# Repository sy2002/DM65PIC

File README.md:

# Firmware for the DM65PIC
## MEGA65 Computer

MEGA65 is an open-source new and open C65-like computer.
All hardware designs and all software are open-source (LGPL).
Please visit www.mega65.org to learn more about it.

## Quickstart

Click here: [How to flash the firmware on the DM65PIC](bin/README.md)

## DM65PIC Peripheral Interface Controller
The DM65PIC is the peripheral interface controller for the MEGA65 computer.
It is based on the [STM32F4 microcontroller](http://www.st.com/stm32f4).

The purpose of the DM65PIC is to provide an interface to an original
Commodore 65 prototype keyboard or a standard C64 keyboard and to provide
joystick ports. Future versions will also be able to work with the MEGA65
custom keyboard and these keyboards will also be able to be used as standard
USB HID devices e.g. while using emulators. Additionally we will implement the
Commodore 65 user port in future versions.

Here is a foto of some prototype version of our custom PCB:

This GitHub repository is containing the firmware of the DM65PIC.

You can see a combination of a MEGA65 FPGA prototype (based on a Nexys 4 DDR
board), a DMPIC65 prototype and a very first work-in-progress version of the
firmware in conjuncton with a real Commodore 65 prototype keyboard in action
on YouTube: [https://youtu.be/5PpsEw80j3M](https://youtu.be/5PpsEw80j3M).

### Folder structure
```
00-STM32F4xx_STANDARD_PERIPHERAL_DRIVERS  STM32 CMSIS and standard peripheral drivers
00-STM32F429_LIBRARIES                    Tilen Majerle's STM32F4 library
01-DM65PIC                                Firmware for the DM65PIC
bin                                       Firmware binary and how-to-flash documentation
eagle                                     Hardware design for the PCB
```

The actual firmware is located within the file `main.c` in the folder
`01-DM65PIC/01-DM65PIC/User`.

### How to flash
In the folder `bin` you always find the latest binary version of the firmware
as a `.hex` file. There is also the file `bin/README.md` that explains you
how to build a cable and how to flash the DM65PIC firmware using a Windows,
OSX or Linux machine.

### How to build
We used the free version of [Keil uVision5](http://www.keil.com/uvision/).
The free version is code-size constrained (32KB), but as our compiled firmware
(including all the libs) is smaller than 32KB, the free version works fine.

After having installed the Keil IDE, just double click or open the file
`project.uvprojx` in the `01-DM65PIC` folder. As all paths are relative, you
should be able to build without further modifications.

### How the interface works
The DM65PIC is doing a matrix scan on the original Commodore 65 keyboard by
letting current flow through the columns and then find out if a key is pressed
by checking, if the current from the column arrives at a certain row. That
means, we configure all "column pins" of the STM32 microcontroller as outputs
(no pullup/pulldown resistor) and all "row pins" as inputs (pulldown
resistor).

The following diagram is the basis for the matrix scan. It is taken from
Commodore's original document
[c65manual.txt](http://www.zimmers.net/cbmpics/cbm/c65/c65manual.txt)
([permalink](https://perma.cc/E5R3-MEXA)),
chapter 2.1.2.

```

            +-----+-----+-----+-----+-----+-----+-----+-----+-----+            +-----+
            | C0  | C1  | C2  | C3  | C4  | C5  | C6  | C7  | C8  |            | GND |
            |PIN20|PIN19|PIN18|PIN17|PIN16|PIN15|PIN14|PIN13|PIN-4|            |PIN-1|
            +--+--+--+--+--+--+--+--+--+--+--+--+--+--+--+--+--+--+            +--+--+
               |     |     |     |     |     |     |     |     |                  |
               |     |     |     |     |     |     |     |     |                  |
               V     V     V     V     V     V     V     V     V                  |
+-----+     +-----+-----+-----+-----+-----+-----+-----+-----+-----+               |
| R0  |<----+ INS |  #  |  %  |  '  |  )  |  +  | œ   |  !  | NO  |               |
|PIN12|     | DEL |  3  |  5  |  7  |  9  |     |     |  1  | SCRL|               |
+-----+     +-----+-----+-----+-----+-----+-----+-----+-----+-----+               |
| R1  |<----+ RET |  W  |  R  |  Y  |  I  |  P  |  *  | <-- | TAB |               |
|PIN11|     |     |     |     |     |     |     |     |     |     |               |
+-----+     +-----+-----+-----+-----+-----+-----+-----+-----+-----+               |
| R2  |<----+ HORZ|  A  |  D  |  G  |  J  |  L  |  ]  | CTRL| ALT |               |
|PIN10|     | CRSR|     |     |     |     |     |  ;  |     |     +----------+    |
+-----+     +-----+-----+-----+-----+-----+-----+-----+-----+-----+          |    |
| R3  |<----+ F8  |  $  |  &  |  {  |  0  |  -  | CLR |  "  | HELP|          |    |
|PIN-9|     | F7  |  4  |  6  |  8  |     |     | HOM |  2  |     |          |    |
+-----+     +-----+-----+-----+-----+-----+-----+-----+-----+-----+          |    |
| R4  |<----+ F2  |  Z  |  C  |  B  |  M  |  >  |RIGHT|SPACE| F10 |          |    |
|PIN-8|     | F1  |     |     |     |     |  .  |SHIFT| BAR | F9  |          |    |
+-----+     +-----+-----+-----+-----+-----+-----+-----+-----+-----+          |    |
| R5  |<----+ F4  |  S  |  F  |  H  |  K  |  [  |  =  | C=  | F12 |          |    |
|PIN-7|     | F3  |     |     |     |     |  :  |     |     | F11 |          |    |
+-----+     +-----+-----+-----+-----+-----+-----+-----+-----+-----+          |    |
| R6  |<----+ F6  |  E  |  T  |  U  |  O  |  @  |  ã  |  Q  | F14 |          |    |
|PIN-6|     | F5  |     |     |     |     |     |  ^  |     | F13 |          |    |
+-----+     +-----+-----+-----+-----+-----+-----+-----+-----+-----+          |    |
| R7  |<----+ VERT|LEFT |  X  |  V  |  N  |  <  |  ?  | RUN | ESC +------+   |    |
|PIN-5|     | CRSR|SHIFT|     |     |     |  ,  |  /  | STOP|     +--+   |   |    |
+-----+     +--+--+--+--+-----+-----+-----+-----+--+--+-----+-----+  |   |   |    |
               |     |                             |                 |   |   |    |
               |     |                             |                 |   |   |    |
               |  +--+--+     /      (LOCKING)     |                 |   |   |    |
               |  |SHIFT+----+  +------------------------------------+   |   |    |
               |  | LOCK|                          |                     |   |    |
               |  +-----+                          |                     |   |    |
               |                             +-----+-----+               |   |    |
            +--+--+                          |           |               |   |    |
            |CRSR +------------+-------------+           +---------------+   |    |
            | UP  |        K1 PIN-21         |           |                   |    |
            +--+--+                          |   4066    |                   |    |
               |                             |  DECODER  |                   |    |
            +--+--+                          |           |                   |    |
            |CRSR +------------+-------------+           +-------------------+    |
            |LEFT |        K2 PIN-22         |           |                        |
            +-----+                          +-----------+                        |
                                                                                  |
+-----+           +-----+     /                                                   |
| NMI | <---------+RESTR+----+  +-------------------------------------------------+
|PIN-3|           |     |                                                         |
+-----+           +-----+                                                         |
                                                                                  |
                                                                                  |
+-----+           +-----+     /      (LOCKING)                                    |
| R8  | <---------+CAPS +----+  +-------------------------------------------------+
|PIN-2|           |LOCK |
+-----+           +-----+

Keyboard Notes:

1. The  64 keys under C0 through C7 occupy the same matrix position as
   in the C/64,  as does the RESTORE key.  Including SHIFT-LOCK, there
   are 66 such keys.

2. The  extended  keyboard consists of the 8 keys under the C8 output.
   Counting the CAPS-LOCK key, there are 9 new keys. The C/64 does not
   scan these keys.

3. The new CURSOR LEFT and CURSOR UP keys simulate a CURSOR plus RIGHT
   SHIFT key combination.

4. The  keyboard mechanism will be mechanically similar to that of the
   C128.
```

While scanning the matrix, the DM65PIC firmware stores the status of each
single key in an array, that is then transmitted to the MEGA65 FPGA using
the Nexys 4 DDR's General Purpose IO (GPIO) port "JB".

The protocol between the DM65PIC and the FPGA works like this: Cyclically,
128-bit are transmitted as 32 (4-bit) nibbles. Each nibble represents 4 bit
within the above-mentioned matrix. Nibble #0 represents the keys INS/DEL,
RET, HORZ/CRSR, F8/F7. Nibble #1 represents F2/F1, F4/F3, F6/F5, VERT/CRSR.
And so on. Here is the full description of the data sequence:

```
nbls #0 - #17:   keyboard bits corresponding to the 9 columns of keys (see above)
nbl #18:         joystick 1: bit0=up, bit1=down, bit2=left, bit3=right
nbl #19:         bit0=joy1 fire, bit2=capslock key status, bit3=restore key status
nbl #20:         joystick 2: bit0=up, bit1=down, bit2=left, bit3=right
nbl #21:         bit0=joy2 fire, bit3=reset momentary-action switch status
nbl #22 onwards: expansion port connector
```

The nibbles are transmitted by setting below-mentioned "bit0" .. "bit3" pins
of the "JB" port and then clocking pin "JB1". For synchronizing the
transmission, the "start of sequence" pin "JB2" is used as soon as a new
128-bit package starts.

The FPGA is also able to communicate back to the DM65PIC, i.e. for transmitting
the LED status; but this is not supported, yet in the current version of the
firmware.

Here is the pin layout for the FPGA's "JB" port:

```
JB1  = PG8:  clock; data must be valid before rising edge
JB2  = PG9:  start of sequence, set to 1 on first nibble of a new 128bit sequence
JB3  = PG10: bit0 of output data nibble
JB4  = PG11: bit1 of output data nibble
JB7  = PG12: bit2 of output data nibble
JB8  = PG13: bit3 of output data nibble
JB9  = PG14: bit 0 of input bit pair
JB10 = PG15: bit 1 of input bit pair
```

### Credits
* [Paul Gardner-Stephen](http://c65gs.blogspot.de): MEGA65 main developer
* [Deft](http://www.m-e-g-a.org/de/mega/profile): chief MEGA65 officer
* doubleflash: DM65PIC hardware design
* [sy2002](http://www.sy2002.de): DM65PIC firmware in this GitHub repository

Special thanks go to [Tilen Majerle](https://github.com/MaJerle) for
supporting sy2002 in learning how to work with the STM32 toolchain and of
course for creating the awesome [STM32F4 library](https://stm32f4-discovery.net)
that we heavily used for creating the DM65PIC firmware.

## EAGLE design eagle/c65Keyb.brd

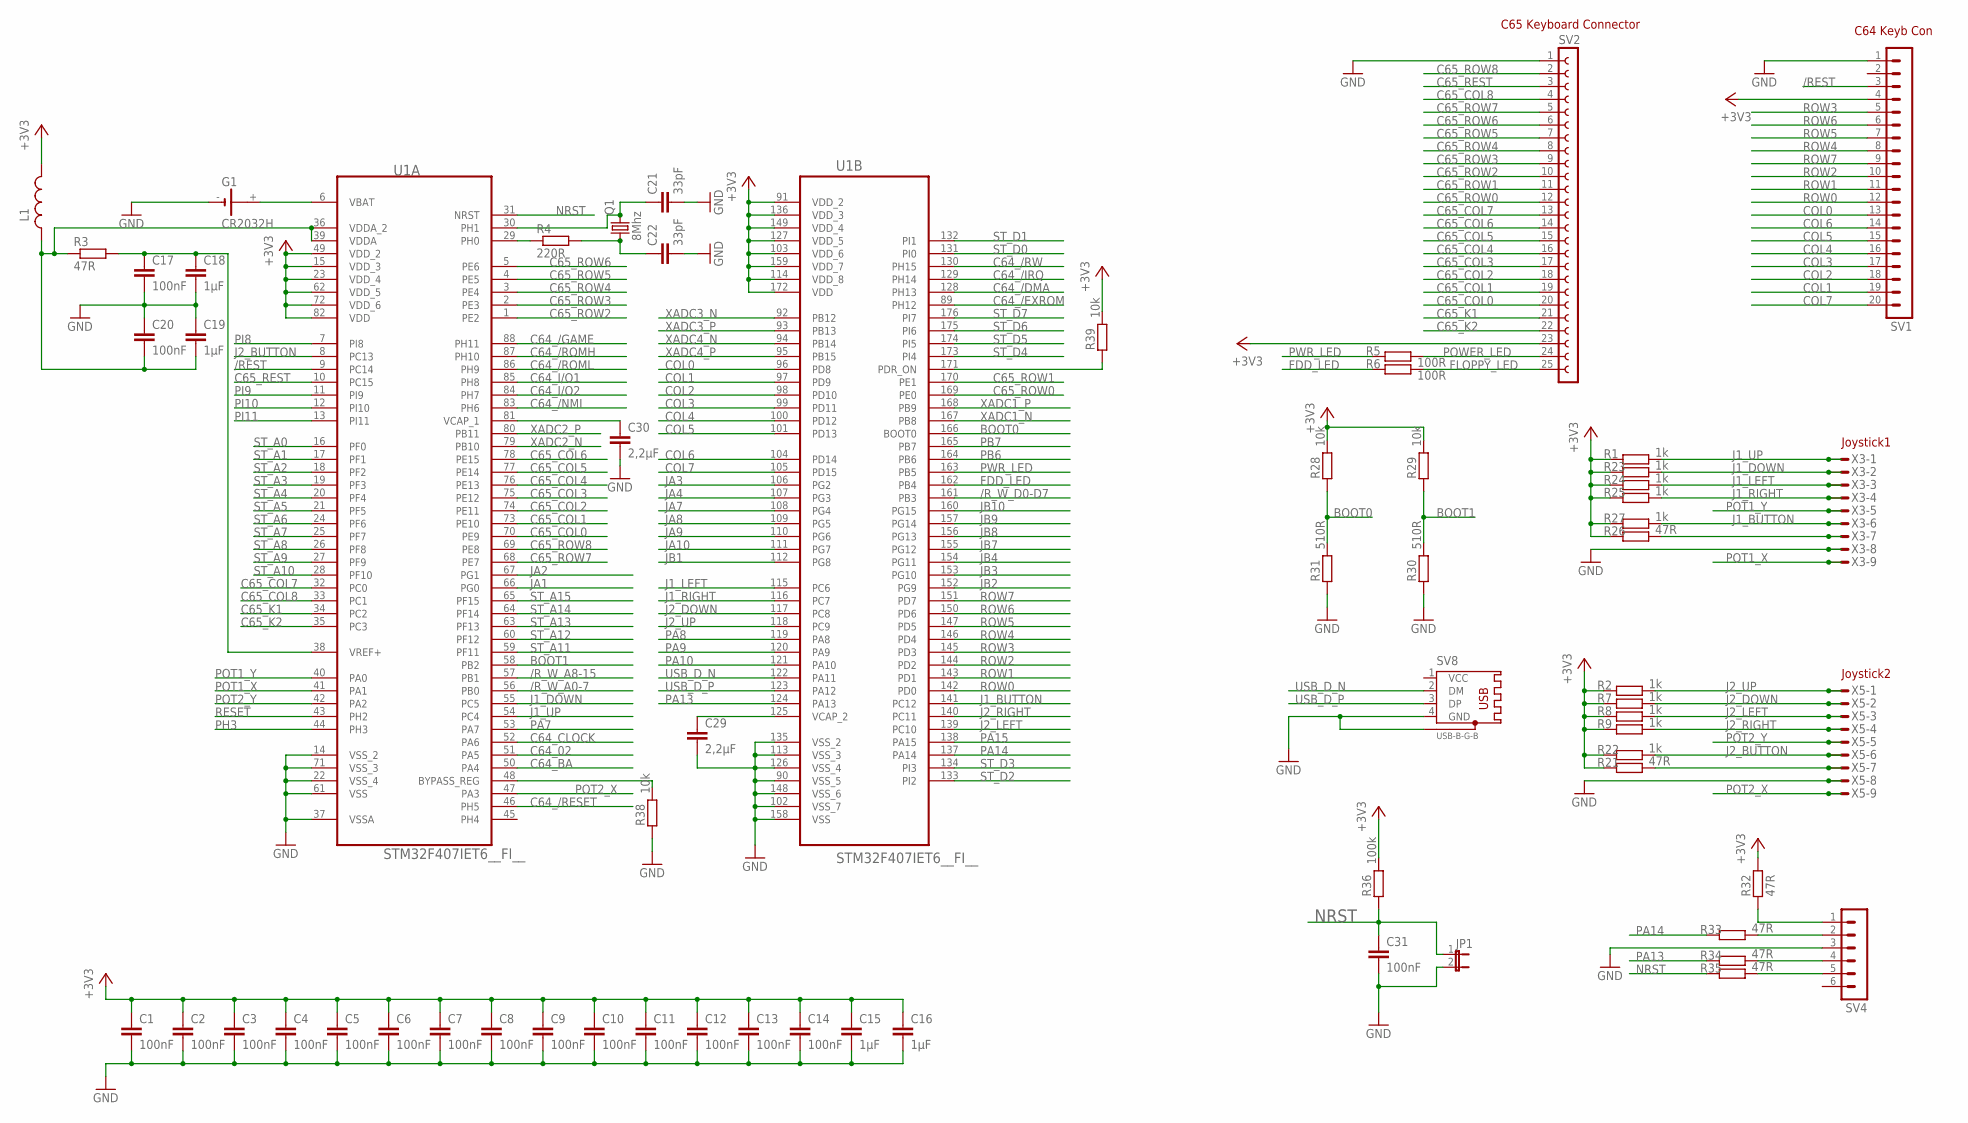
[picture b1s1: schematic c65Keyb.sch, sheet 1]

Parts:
C1, C2, C3, C4, C5, C6, C7, C8, C9, C10, C11, C12, C13, C14, C17, C20, C31: 100nF; C0805
C15, C16, C18, C19: 1µF; C0805
C21, C22: 33pF; C0805
C29, C30: 2,2µF; C0805
G1: CR2032H
JP1: JP1E; JP1
L1: L-0805A; SMD0805-ALT
Q1: 8Mhz; HC49UP
R1, R2, R7, R8, R9, R22, R23, R24, R25, R27: 1k; R0805
R3, R21, R26, R32, R33, R34, R35: 47R; R0805
R4: 220R; R0805
R5, R6: 100R; R0805
R28, R29, R38, R39: 10k; R0805
R30, R31: 510R; R0805
R36: 100k; R0805
SV1: MA20-1
SV2: C65_MOLEX_KEYB
SV4: MA06-1
SV8: USB-B-G-B; USB-B-THG-01
U1: STM32F407IET6__FI__; QFP176
X3, X5: M09-182S; 182-009-MALE

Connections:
+3V3: C1.1, C2.1, C3.1, C4.1, C5.1, C6.1, C7.1, C8.1, C9.1, C10.1, C11.1, C12.1, C13.1, C14.1, C15.1, C16.1, L1.2, R1.1, R2.1, R7.1, R8.1, R9.1, R21.1, R22.1, R23.1, R24.1, R25.1, R26.1, R27.1, R28.2, R29.2, R32.2, R36.2, R39.2, SV1.4, SV2.23, U1.15 (VDD_3), U1.23 (VDD_4), U1.49 (VDD_2), U1.62 (VDD_5), U1.72 (VDD_6), U1.82 (VDD), U1.91 (VDD_2), U1.103 (VDD_6), U1.114 (VDD_8), U1.127 (VDD_5), U1.136 (VDD_3), U1.149 (VDD_4), U1.159 (VDD_7), U1.172 (VDD); also elsewhere on the board
/REST: SV1.3, U1.9 (PC14)
/R_W_A0-7: U1.56 (PB0); also elsewhere on the board
/R_W_A8-15: U1.57 (PB1); also elsewhere on the board
/R_W_D0-D7: U1.161 (PB3); also elsewhere on the board
BOOT0: R28.1, R31.2, U1.166 (BOOT0)
BOOT1: R29.1, R30.2, U1.58 (PB2)
C64_02: U1.51 (PA5); also elsewhere on the board
C64_/DMA: U1.128 (PH13); also elsewhere on the board
C64_/EXROM: U1.89 (PH12); also elsewhere on the board
C64_/GAME: U1.88 (PH11); also elsewhere on the board
C64_/IRQ: U1.129 (PH14); also elsewhere on the board
C64_/NMI: U1.83 (PH6); also elsewhere on the board
C64_/RESET: U1.46 (PH5); also elsewhere on the board
C64_/ROMH: U1.87 (PH10); also elsewhere on the board
C64_/ROML: U1.86 (PH9); also elsewhere on the board
C64_/RW: U1.130 (PH15); also elsewhere on the board
C64_BA: U1.50 (PA4); also elsewhere on the board
C64_CLOCK: U1.52 (PA6); also elsewhere on the board
C64_I/O1: U1.85 (PH8); also elsewhere on the board
C64_I/O2: U1.84 (PH7); also elsewhere on the board
C65_COL0: SV2.20, U1.70 (PE9)
C65_COL1: SV2.19, U1.73 (PE10)
C65_COL2: SV2.18, U1.74 (PE11)
C65_COL3: SV2.17, U1.75 (PE12)
C65_COL4: SV2.16, U1.76 (PE13)
C65_COL5: SV2.15, U1.77 (PE14)
C65_COL6: SV2.14, U1.78 (PE15)
C65_COL7: SV2.13, U1.32 (PC0)
C65_COL8: SV2.4, U1.33 (PC1)
C65_K1: SV2.21, U1.34 (PC2)
C65_K2: SV2.22, U1.35 (PC3)
C65_REST: SV2.3, U1.10 (PC15)
C65_ROW0: SV2.12, U1.169 (PE0)
C65_ROW1: SV2.11, U1.170 (PE1)
C65_ROW2: SV2.10, U1.1 (PE2)
C65_ROW3: SV2.9, U1.2 (PE3)
C65_ROW4: SV2.8, U1.3 (PE4)
C65_ROW5: SV2.7, U1.4 (PE5)
C65_ROW6: SV2.6, U1.5 (PE6)
C65_ROW7: SV2.5, U1.68 (PE7)
C65_ROW8: SV2.2, U1.69 (PE8)
COL0: SV1.13, U1.96 (PD8)
COL1: SV1.19, U1.97 (PD9)
COL2: SV1.18, U1.98 (PD10)
COL3: SV1.17, U1.99 (PD11)
COL4: SV1.16, U1.100 (PD12)
COL5: SV1.15, U1.101 (PD13)
COL6: SV1.14, U1.104 (PD14)
COL7: SV1.20, U1.105 (PD15)
FDD_LED: R6.1, U1.162 (PB4)
FLOPPY_LED: R6.2, SV2.25
GND: C1.2, C2.2, C3.2, C4.2, C5.2, C6.2, C7.2, C8.2, C9.2, C10.2, C11.2, C12.2, C13.2, C14.2, C15.2, C16.2, C17.2, C18.2, C19.1, C20.1, C21.2, C22.2, C29.2, C30.2, C31.2, G1.-, JP1.2, R30.1, R31.1, R38.1, SV1.1, SV2.1, SV4.3, SV8.4 (GND), SV8.G1, U1.14 (VSS_2), U1.22 (VSS_4), U1.37 (VSSA), U1.61 (VSS), U1.71 (VSS_3), U1.90 (VSS_5), U1.102 (VSS_7), U1.113 (VSS_3), U1.126 (VSS_4), U1.135 (VSS_2), U1.148 (VSS_6), U1.158 (VSS), X3.8, X5.8; also elsewhere on the board
J1_BUTTON: R27.2, U1.141 (PC12), X3.6
J1_DOWN: R23.2, U1.55 (PC5), X3.2
J1_LEFT: R24.2, U1.115 (PC6), X3.3
J1_RIGHT: R25.2, U1.116 (PC7), X3.4
J1_UP: R1.2, U1.54 (PC4), X3.1
J2_BUTTON: R22.2, U1.8 (PC13), X5.6
J2_DOWN: R7.2, U1.117 (PC8), X5.2
J2_LEFT: R8.2, U1.139 (PC10), X5.3
J2_RIGHT: R9.2, U1.140 (PC11), X5.4
J2_UP: R2.2, U1.118 (PC9), X5.1
JA1: U1.66 (PG0); also elsewhere on the board
JA2: U1.67 (PG1); also elsewhere on the board
JA3: U1.106 (PG2); also elsewhere on the board
JA4: U1.107 (PG3); also elsewhere on the board
JA7: U1.108 (PG4); also elsewhere on the board
JA8: U1.109 (PG5); also elsewhere on the board
JA9: U1.110 (PG6); also elsewhere on the board
JA10: U1.111 (PG7); also elsewhere on the board
JB1: U1.112 (PG8); also elsewhere on the board
JB2: U1.152 (PG9); also elsewhere on the board
JB3: U1.153 (PG10); also elsewhere on the board
JB4: U1.154 (PG11); also elsewhere on the board
JB7: U1.155 (PG12); also elsewhere on the board
JB8: U1.156 (PG13); also elsewhere on the board
JB9: U1.157 (PG14); also elsewhere on the board
JB10: U1.160 (PG15); also elsewhere on the board
unnamed: G1.+, U1.6 (VBAT)
unnamed: R4.1, U1.29 (PH0)
unnamed: C17.1, C18.1, R3.2, U1.38 (VREF+)
unnamed: R21.2, X5.7
unnamed: C30.1, U1.81 (VCAP_1)
unnamed: C29.1, U1.125 (VCAP_2)
unnamed: R32.1, SV4.1
unnamed: R33.2, SV4.2
unnamed: R34.2, SV4.4
unnamed: R26.2, X3.7
unnamed: R35.2, SV4.5
unnamed: R38.2, U1.48 (BYPASS_REG)
unnamed: C21.1, Q1.2, U1.30 (PH1)
unnamed: C22.1, Q1.1, R4.2
unnamed: R39.1, U1.171 (PDR_ON)
unnamed: C19.2, C20.2, L1.1, R3.1, U1.36 (VDDA_2), U1.39 (VDDA)
NRST: C31.1, JP1.1, R35.1, R36.1, U1.31 (NRST)
PA7: U1.53 (PA7); also elsewhere on the board
PA8: U1.119 (PA8); also elsewhere on the board
PA9: U1.120 (PA9); also elsewhere on the board
PA10: U1.121 (PA10); also elsewhere on the board
PA13: R34.1, U1.124 (PA13)
PA14: R33.1, U1.137 (PA14)
PA15: U1.138 (PA15); also elsewhere on the board
PB6: U1.164 (PB6); also elsewhere on the board
PB7: U1.165 (PB7); also elsewhere on the board
PH3: U1.44 (PH3); also elsewhere on the board
PI8: U1.7 (PI8); also elsewhere on the board
PI9: U1.11 (PI9); also elsewhere on the board
PI10: U1.12 (PI10); also elsewhere on the board
PI11: U1.13 (PI11); also elsewhere on the board
POT1_X: U1.41 (PA1), X3.9
POT1_Y: U1.40 (PA0), X3.5
POT2_X: U1.47 (PA3), X5.9
POT2_Y: U1.42 (PA2), X5.5
POWER_LED: R5.2, SV2.24
PWR_LED: R5.1, U1.163 (PB5)
RESET: U1.43 (PH2); also elsewhere on the board
ROW0: SV1.12, U1.142 (PD0)
ROW1: SV1.11, U1.143 (PD1)
ROW2: SV1.10, U1.144 (PD2)
ROW3: SV1.5, U1.145 (PD3)
ROW4: SV1.8, U1.146 (PD4)
ROW5: SV1.7, U1.147 (PD5)
ROW6: SV1.6, U1.150 (PD6)
ROW7: SV1.9, U1.151 (PD7)
ST_A0: U1.16 (PF0); also elsewhere on the board
ST_A1: U1.17 (PF1); also elsewhere on the board
ST_A2: U1.18 (PF2); also elsewhere on the board
ST_A3: U1.19 (PF3); also elsewhere on the board
ST_A4: U1.20 (PF4); also elsewhere on the board
ST_A5: U1.21 (PF5); also elsewhere on the board
ST_A6: U1.24 (PF6); also elsewhere on the board
ST_A7: U1.25 (PF7); also elsewhere on the board
ST_A8: U1.26 (PF8); also elsewhere on the board
ST_A9: U1.27 (PF9); also elsewhere on the board
ST_A10: U1.28 (PF10); also elsewhere on the board
ST_A11: U1.59 (PF11); also elsewhere on the board
ST_A12: U1.60 (PF12); also elsewhere on the board
ST_A13: U1.63 (PF13); also elsewhere on the board
ST_A14: U1.64 (PF14); also elsewhere on the board
ST_A15: U1.65 (PF15); also elsewhere on the board
ST_D0: U1.131 (PI0); also elsewhere on the board
ST_D1: U1.132 (PI1); also elsewhere on the board
ST_D2: U1.133 (PI2); also elsewhere on the board
ST_D3: U1.134 (PI3); also elsewhere on the board
ST_D4: U1.173 (PI4); also elsewhere on the board
ST_D5: U1.174 (PI5); also elsewhere on the board
ST_D6: U1.175 (PI6); also elsewhere on the board
ST_D7: U1.176 (PI7); also elsewhere on the board
USB_D_N: SV8.2 (DM), U1.122 (PA11)
USB_D_P: SV8.3 (DP), U1.123 (PA12)
XADC1_N: U1.167 (PB8); also elsewhere on the board
XADC1_P: U1.168 (PB9); also elsewhere on the board
XADC2_N: U1.79 (PB10); also elsewhere on the board
XADC2_P: U1.80 (PB11); also elsewhere on the board
XADC3_N: U1.92 (PB12); also elsewhere on the board
XADC3_P: U1.93 (PB13); also elsewhere on the board
XADC4_N: U1.94 (PB14); also elsewhere on the board
XADC4_P: U1.95 (PB15); also elsewhere on the board

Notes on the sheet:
C64 Keyb Con
Joystick1
Joystick2
C65 Keyboard Connector

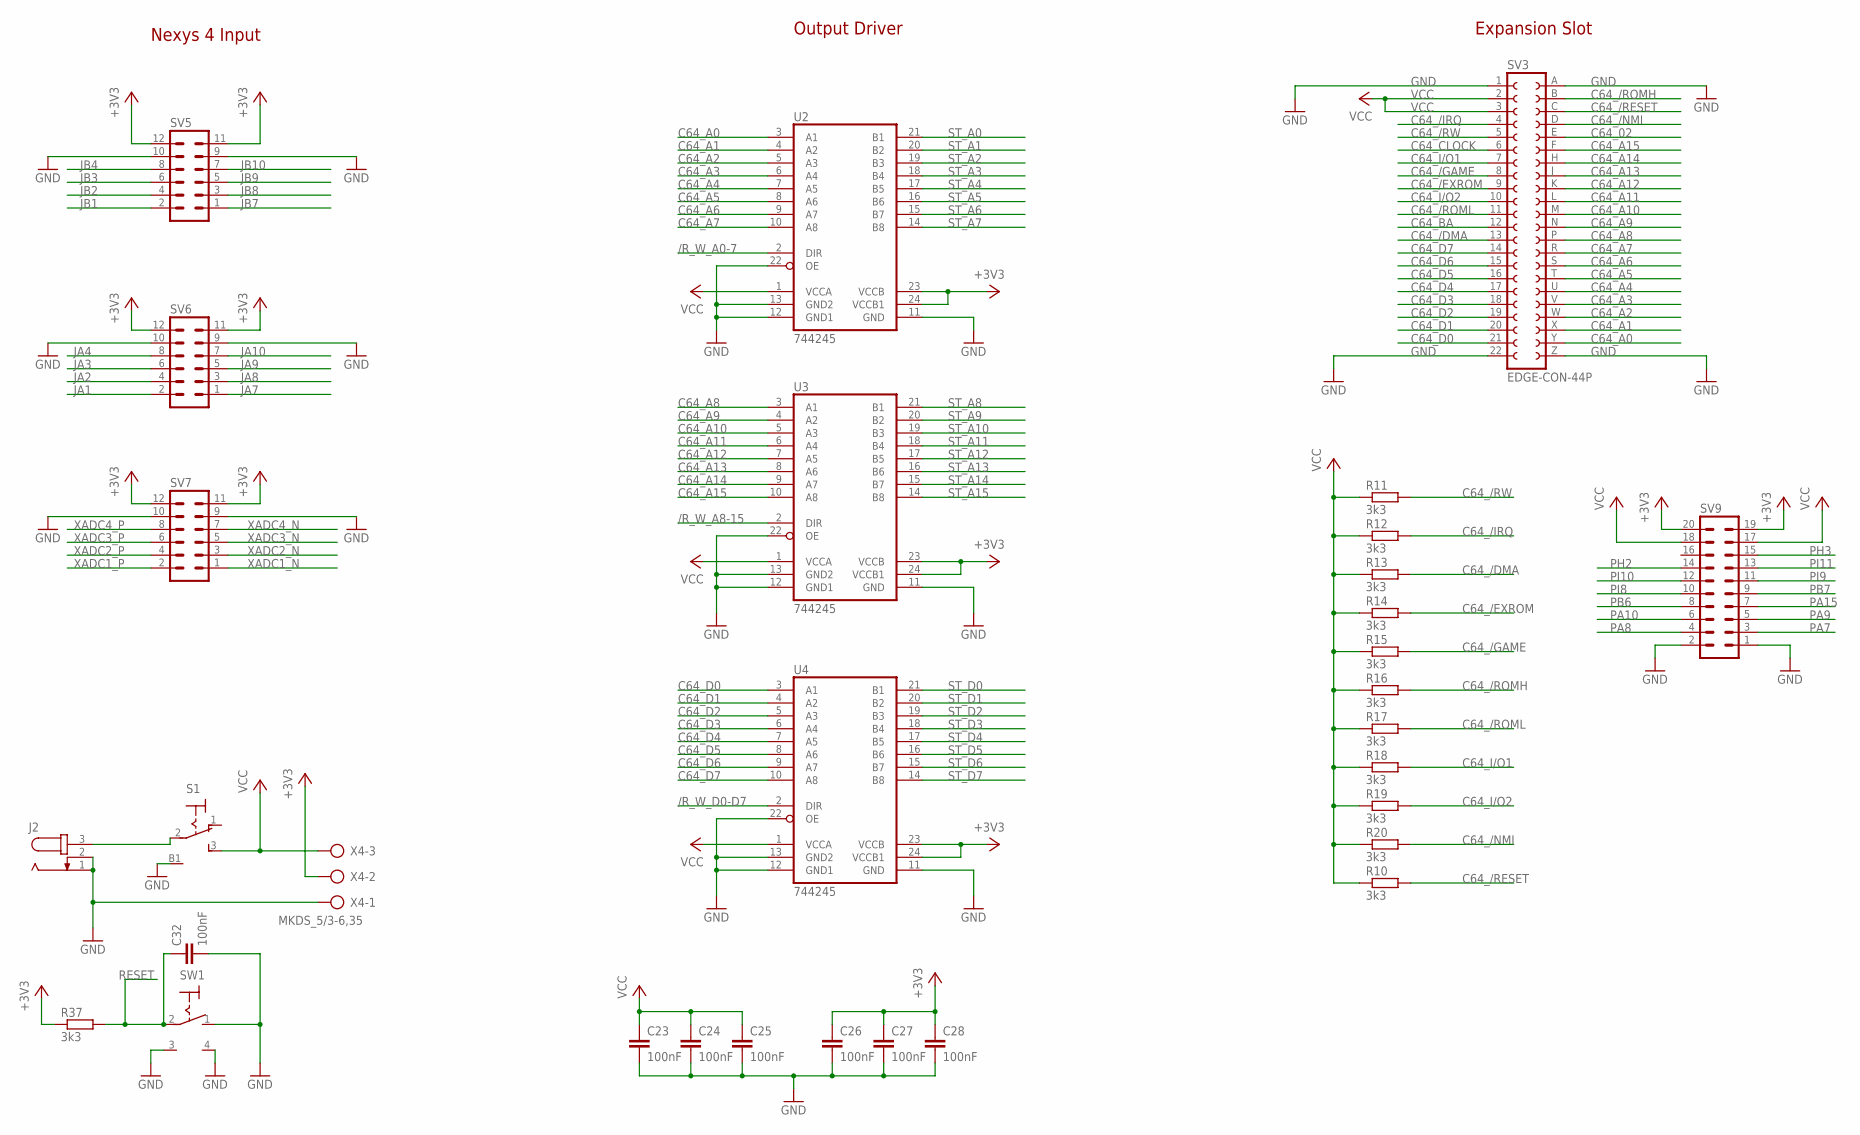
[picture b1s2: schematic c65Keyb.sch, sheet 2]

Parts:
C23, C24, C25, C26, C27, C28, C32: 100nF; C0805
J2: JACK-PLUG1; SPC4078
R10, R11, R12, R13, R14, R15, R16, R17, R18, R19, R20, R37: 3k3; R0805
S1: LPV-1
SV3: EDGE-CON-44P; EDGE-CON-44
SV5, SV6, SV7: MA06-2W
SV9: MA10-2
SW1: TASTER; MICRO_SWITCH
U2, U3, U4: 744245; SO24L
X4: MKDS_5/3-6,35; MKDS_5/3-635

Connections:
+3V3: C26.1, C27.1, C28.1, R37.1, SV5.11, SV5.12, SV6.11, SV6.12, SV7.11, SV7.12, SV9.19, SV9.20, U2.23 (VCCB), U2.24 (VCCB1), U3.23 (VCCB), U3.24 (VCCB1), U4.23 (VCCB), U4.24 (VCCB1), X4.2; also elsewhere on the board
/R_W_A0-7: U2.2 (DIR); also elsewhere on the board
/R_W_A8-15: U3.2 (DIR); also elsewhere on the board
/R_W_D0-D7: U4.2 (DIR); also elsewhere on the board
C64_02: SV3.E; also elsewhere on the board
C64_/DMA: R13.2, SV3.13; also elsewhere on the board
C64_/EXROM: R14.2, SV3.9; also elsewhere on the board
C64_/GAME: R15.2, SV3.8; also elsewhere on the board
C64_/IRQ: R12.2, SV3.4; also elsewhere on the board
C64_/NMI: R20.2, SV3.D; also elsewhere on the board
C64_/RESET: R10.2, SV3.C; also elsewhere on the board
C64_/ROMH: R16.2, SV3.B; also elsewhere on the board
C64_/ROML: R17.2, SV3.11; also elsewhere on the board
C64_/RW: R11.2, SV3.5; also elsewhere on the board
C64_A0: SV3.Y, U2.3 (A1)
C64_A1: SV3.X, U2.4 (A2)
C64_A2: SV3.W, U2.5 (A3)
C64_A3: SV3.V, U2.6 (A4)
C64_A4: SV3.U, U2.7 (A5)
C64_A5: SV3.T, U2.8 (A6)
C64_A6: SV3.S, U2.9 (A7)
C64_A7: SV3.R, U2.10 (A8)
C64_A8: SV3.P, U3.3 (A1)
C64_A9: SV3.N, U3.4 (A2)
C64_A10: SV3.M, U3.5 (A3)
C64_A11: SV3.L, U3.6 (A4)
C64_A12: SV3.K, U3.7 (A5)
C64_A13: SV3.J, U3.8 (A6)
C64_A14: SV3.H, U3.9 (A7)
C64_A15: SV3.F, U3.10 (A8)
C64_BA: SV3.12; also elsewhere on the board
C64_CLOCK: SV3.6; also elsewhere on the board
C64_D0: SV3.21, U4.3 (A1)
C64_D1: SV3.20, U4.4 (A2)
C64_D2: SV3.19, U4.5 (A3)
C64_D3: SV3.18, U4.6 (A4)
C64_D4: SV3.17, U4.7 (A5)
C64_D5: SV3.16, U4.8 (A6)
C64_D6: SV3.15, U4.9 (A7)
C64_D7: SV3.14, U4.10 (A8)
C64_I/O1: R18.2, SV3.7; also elsewhere on the board
C64_I/O2: R19.2, SV3.10; also elsewhere on the board
GND: C23.2, C24.2, C25.2, C26.2, C27.2, C28.2, C32.2, J2.1, J2.2, S1.B1 (B), SV3.1, SV3.22, SV3.A, SV3.Z, SV5.9, SV5.10, SV6.9, SV6.10, SV7.9, SV7.10, SV9.1, SV9.2, SW1.1 (O), SW1.3 (B), SW1.4 (B1), U2.11 (GND), U2.12 (GND1), U2.13 (GND2), U2.22 (OE), U3.11 (GND), U3.12 (GND1), U3.13 (GND2), U3.22 (OE), U4.11 (GND), U4.12 (GND1), U4.13 (GND2), U4.22 (OE), X4.1; also elsewhere on the board
JA1: SV6.2; also elsewhere on the board
JA2: SV6.4; also elsewhere on the board
JA3: SV6.6; also elsewhere on the board
JA4: SV6.8; also elsewhere on the board
JA7: SV6.1; also elsewhere on the board
JA8: SV6.3; also elsewhere on the board
JA9: SV6.5; also elsewhere on the board
JA10: SV6.7; also elsewhere on the board
JB1: SV5.2; also elsewhere on the board
JB2: SV5.4; also elsewhere on the board
JB3: SV5.6; also elsewhere on the board
JB4: SV5.8; also elsewhere on the board
JB7: SV5.1; also elsewhere on the board
JB8: SV5.3; also elsewhere on the board
JB9: SV5.5; also elsewhere on the board
JB10: SV5.7; also elsewhere on the board
unnamed: J2.3, S1.2
PA7: SV9.3; also elsewhere on the board
PA8: SV9.4; also elsewhere on the board
PA9: SV9.5; also elsewhere on the board
PA10: SV9.6; also elsewhere on the board
PA15: SV9.7; also elsewhere on the board
PB6: SV9.8; also elsewhere on the board
PB7: SV9.9; also elsewhere on the board
PH2: SV9.14
PH3: SV9.15; also elsewhere on the board
PI8: SV9.10; also elsewhere on the board
PI9: SV9.11; also elsewhere on the board
PI10: SV9.12; also elsewhere on the board
PI11: SV9.13; also elsewhere on the board
RESET: C32.1, R37.2, SW1.2; also elsewhere on the board
ST_A0: U2.21 (B1); also elsewhere on the board
ST_A1: U2.20 (B2); also elsewhere on the board
ST_A2: U2.19 (B3); also elsewhere on the board
ST_A3: U2.18 (B4); also elsewhere on the board
ST_A4: U2.17 (B5); also elsewhere on the board
ST_A5: U2.16 (B6); also elsewhere on the board
ST_A6: U2.15 (B7); also elsewhere on the board
ST_A7: U2.14 (B8); also elsewhere on the board
ST_A8: U3.21 (B1); also elsewhere on the board
ST_A9: U3.20 (B2); also elsewhere on the board
ST_A10: U3.19 (B3); also elsewhere on the board
ST_A11: U3.18 (B4); also elsewhere on the board
ST_A12: U3.17 (B5); also elsewhere on the board
ST_A13: U3.16 (B6); also elsewhere on the board
ST_A14: U3.15 (B7); also elsewhere on the board
ST_A15: U3.14 (B8); also elsewhere on the board
ST_D0: U4.21 (B1); also elsewhere on the board
ST_D1: U4.20 (B2); also elsewhere on the board
ST_D2: U4.19 (B3); also elsewhere on the board
ST_D3: U4.18 (B4); also elsewhere on the board
ST_D4: U4.17 (B5); also elsewhere on the board
ST_D5: U4.16 (B6); also elsewhere on the board
ST_D6: U4.15 (B7); also elsewhere on the board
ST_D7: U4.14 (B8); also elsewhere on the board
VCC: C23.1, C24.1, C25.1, R10.1, R11.1, R12.1, R13.1, R14.1, R15.1, R16.1, R17.1, R18.1, R19.1, R20.1, S1.3 (S), SV3.2, SV3.3, SV9.17, SV9.18, U2.1 (VCCA), U3.1 (VCCA), U4.1 (VCCA), X4.3
XADC1_N: SV7.1; also elsewhere on the board
XADC1_P: SV7.2; also elsewhere on the board
XADC2_N: SV7.3; also elsewhere on the board
XADC2_P: SV7.4; also elsewhere on the board
XADC3_N: SV7.5; also elsewhere on the board
XADC3_P: SV7.6; also elsewhere on the board
XADC4_N: SV7.7; also elsewhere on the board
XADC4_P: SV7.8; also elsewhere on the board

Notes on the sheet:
Expansion Slot
Output Driver
Nexys 4 Input

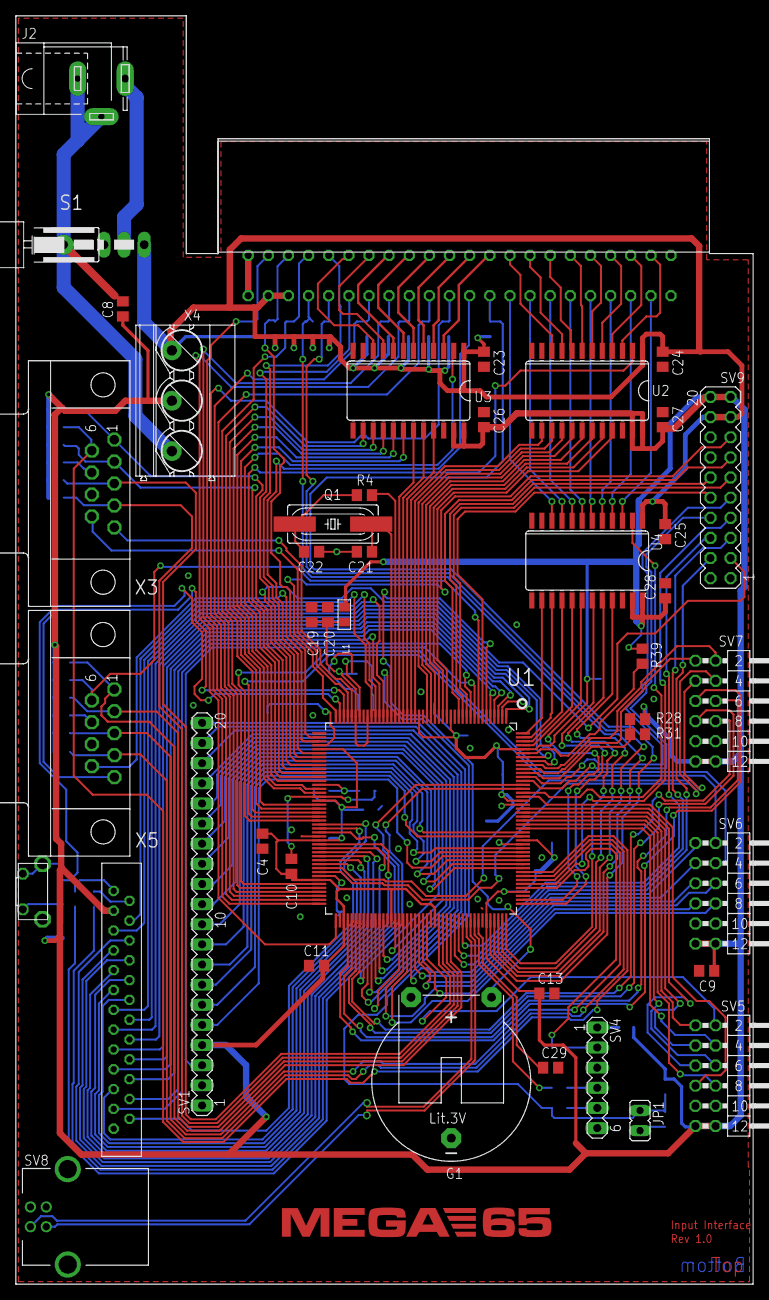
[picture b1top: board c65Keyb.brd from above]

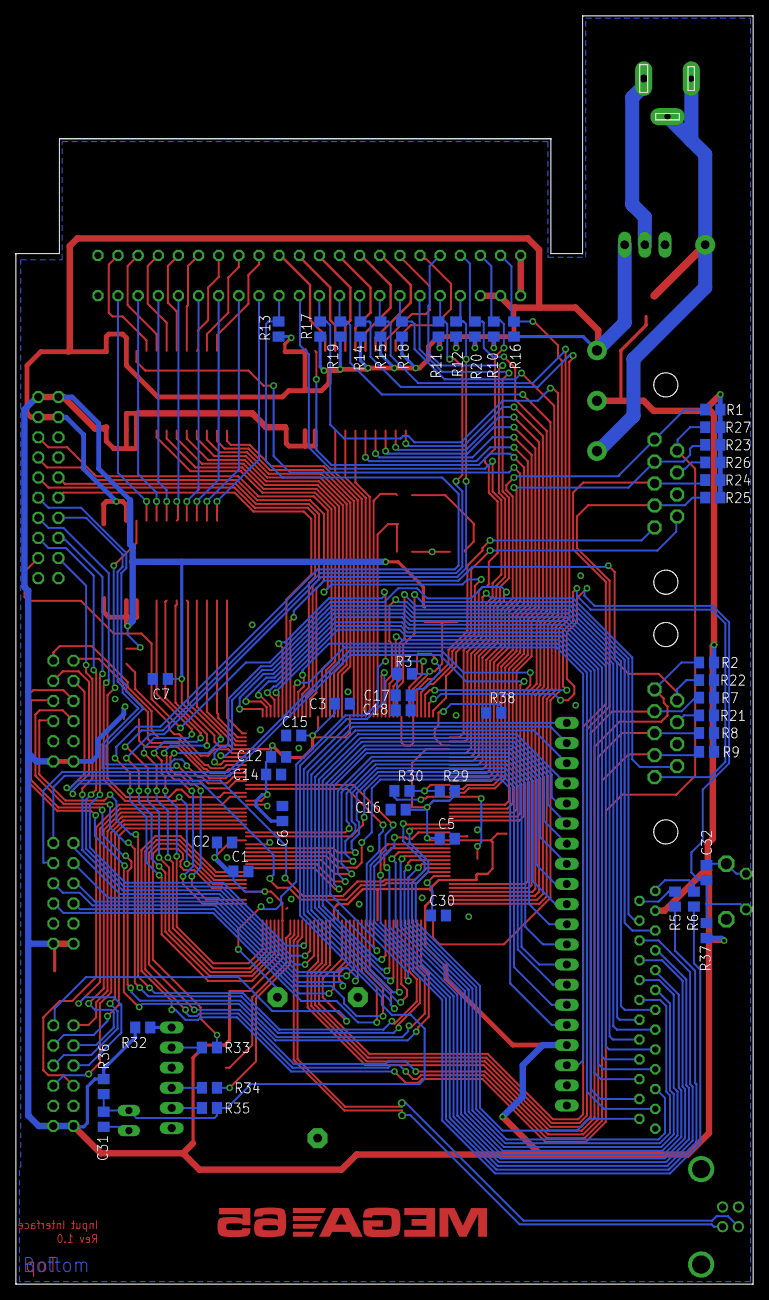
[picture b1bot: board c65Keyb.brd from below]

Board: 2 copper layers, 93.0 x 160.0 mm, 94 parts (50 on the bottom side), 185 nets.

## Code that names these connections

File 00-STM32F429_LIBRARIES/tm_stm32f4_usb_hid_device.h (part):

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USB			|STM32F4xx FS mode				|STM32F4xx HS in FS mode	|Notes
			|STM32F4-Discovery				|STM32F429-Discovery

Data +		PA12							PB15						Data+ for USB, standard and used pin
Data -		PA11							PB14						Data- for USB, standard and used pin
ID			PA10							PB12						ID pin, used on F4 and F429 discovery boards, not needed if you don't like it
VBUS		PA9								PB13						VBUS pin, used on F4 and F429 discovery board for activating USB chip.
	
@endverbatim
 *
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
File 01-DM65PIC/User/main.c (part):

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    TM_GPIO_Init(LEDs[ledFDD].GPIOx, LEDs[ledFDD].GPIO_Pin, TM_GPIO_Mode_OUT, TM_GPIO_OType_PP, TM_GPIO_PuPd_NOPULL, TM_GPIO_Speed_Low);
    
    /* Initialize outputs for communicating with the FPGA via GPIO port JB for debugging    
        JB1  = PG8: clock; data must be valid before rising edge
        JB2  = PG9: start of sequence, set to 1 when the first nibble of a new 128bit sequence is presented
        JB3  = PG10: bit0 of output data nibble
        JB4  = PG11: bit1 of output data nibble
        JB7  = PG12: bit2 of output data nibble
        JB8  = PG13: bit3 of output data nibble
        JB9  = PG14: bit 0 of input bit pair
        JB10 = PG15: bit 1 of input bit pair
    */
  
    #define P_CLOCK     GPIO_Pin_8
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
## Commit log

2015-09-27 Initial commit: Basic keyboard functionality (special keys are still wip)
2015-09-27 corrected .gitignore to exclude temporary build files
2015-09-27 created README.md
2015-09-27 wrote detailed README.md
2015-09-27 cursor keys are working
2015-09-27 improved documentation
2015-09-27 restore key works
2015-09-27 all keys (incl. C65 specific) plus joysticks working
2015-09-27 added firmware binary and how-to-flash instructions
2015-10-03 added how-to-build-a-cable documentation
2015-10-03 created VERSIONS file
2015-10-03 support for C64 standard keyboards and joyport swapping
2015-10-04 added LED support and updated the eagle schematics
2015-10-06 inverted the LED logic
2018-11-20 fixed broken link to Tilen Majerle's library documentation
2018-11-20 added permalink to c65 documentation
2018-11-20 fixed documentation
2021-07-11 Update README.md
    Added Quickstart link

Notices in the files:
00-STM32F429_LIBRARIES/tm_stm32f4_usb_hid_device.h:
@license GNU GPL v3
Copyright (C) Tilen Majerle, 2015
This program is free software: you can redistribute it and/or modify
it under the terms of the GNU General Public License as published by
the Free Software Foundation, either version 3 of the License, or
any later version.
